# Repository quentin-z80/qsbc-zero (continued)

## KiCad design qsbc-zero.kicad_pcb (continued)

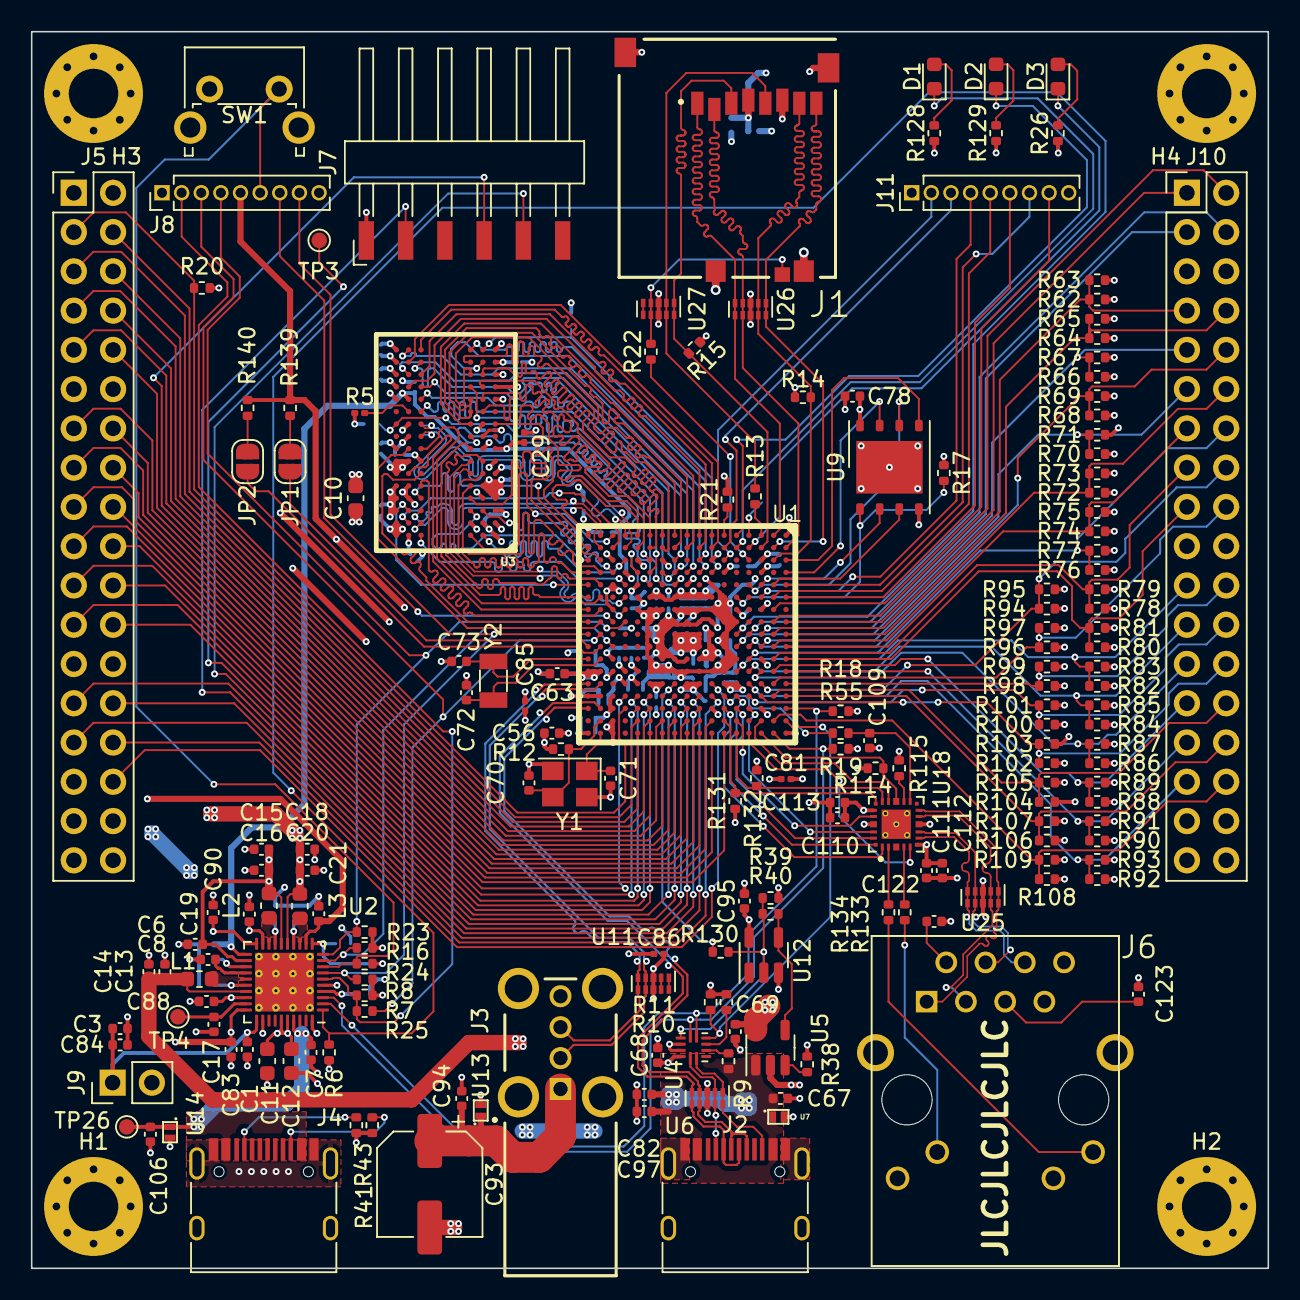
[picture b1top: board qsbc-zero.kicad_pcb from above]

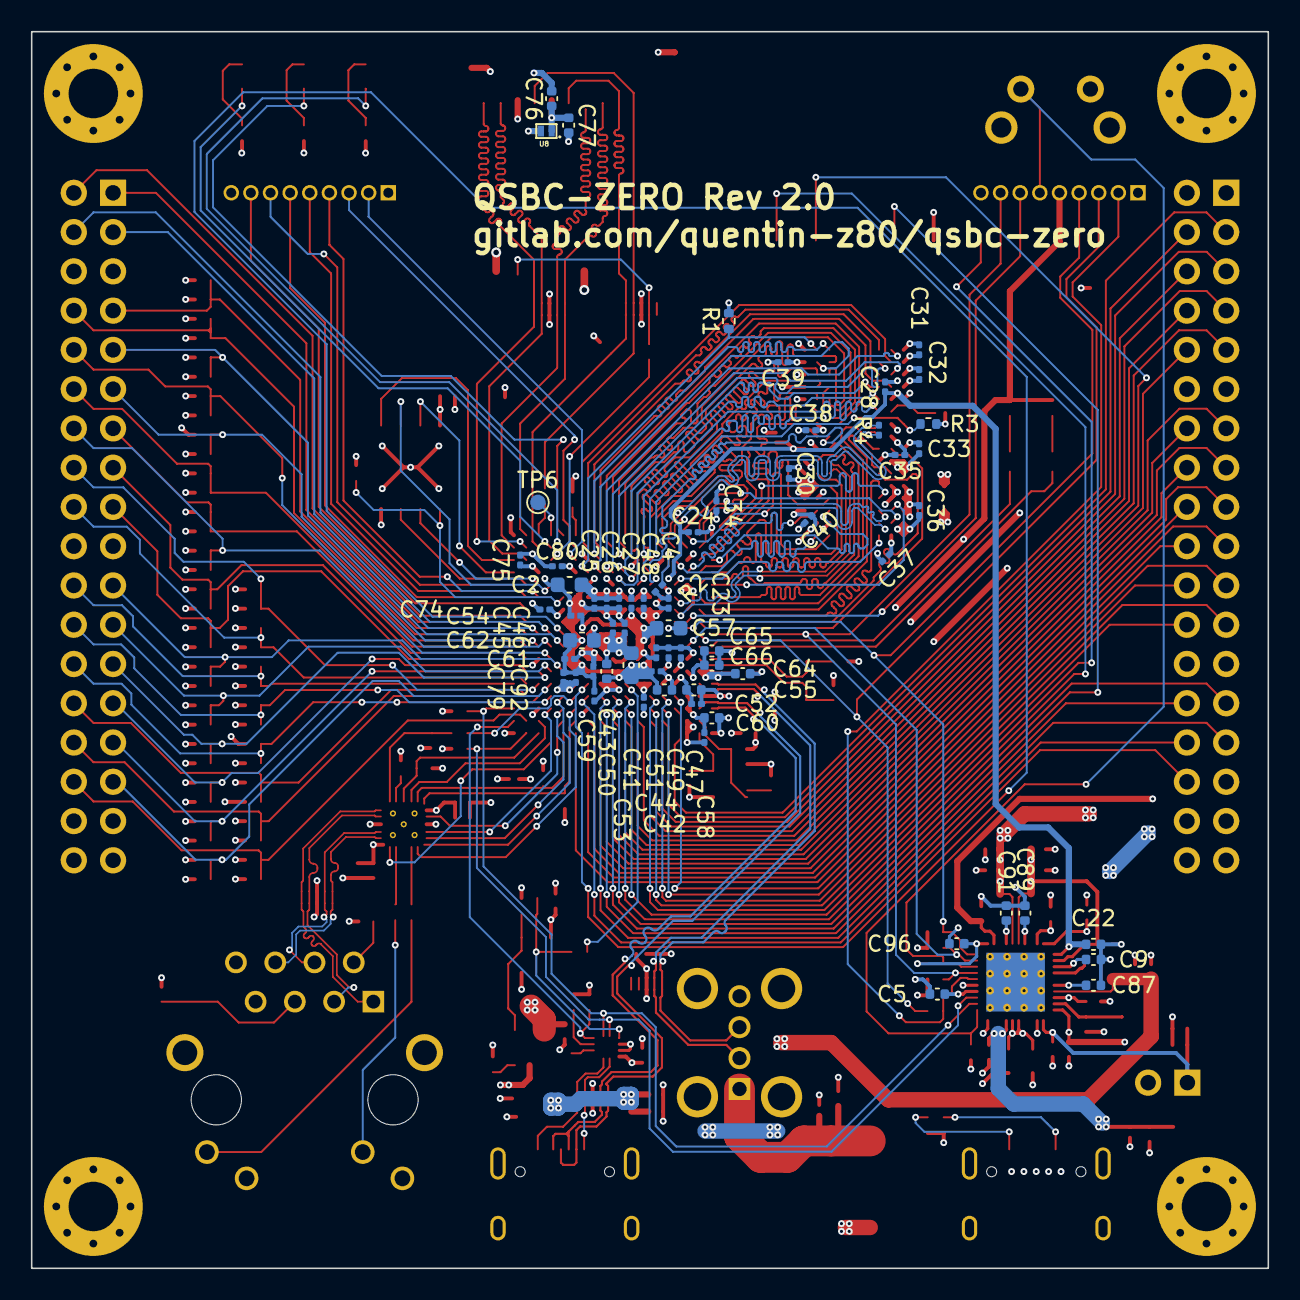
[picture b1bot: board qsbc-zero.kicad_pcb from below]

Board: 4 copper layers, 80.0 x 80.0 mm, 243 parts (63 on the bottom side), 219 nets.

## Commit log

2021-12-24 first ddr routing attempt
2021-12-30 more ddr routing, add more connectors
2022-01-01 start moving to hierarchal labels, add emmc
2022-01-06 move to hierarchal labels, work on power tree, add basic pcb layout
2022-01-06 remove auto save file
2022-01-09 most of sch done, inital component pcb placement
2022-02-06 lots of routing, ddr length matching done
2022-02-15 more pcb work, bom work
2022-02-25 add basic readme, rev 1 of pcb
2022-03-01 remove uneeded symbols, footprints, and 3d models
2022-03-15 misc fixes, add pics of board
2022-03-15 Add LICENSE
2022-03-17 update readme todos
2022-03-19 u-boot: ethernet now working
2022-03-19 add steps to flash u-boot
2022-03-19 README: fix u-boot flash step typo
2022-03-24 README: cleanup build instructions
2022-04-03 misc rev2 fixes
2022-04-05 fix cap PN
2022-04-05 tusb320: fix swaped SDA/SCL
2022-04-05 tusb320: use drp mode
2022-08-09 cleanup schematic junk
2022-08-09 README.md: add pcb manufacturing info
2022-11-30 README.md: fix stackup typo, add to todo list
2023-01-16 add photo of blank board
